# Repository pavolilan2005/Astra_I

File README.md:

# Astra_I
Diseño y desarrollo de un CubeSat experimental de bajo costo, basado en una OBC STM32F411, orientado a adquisición de datos atmosféricos, telemetría LoRa y desarrollo de tecnologías espaciales accesibles.

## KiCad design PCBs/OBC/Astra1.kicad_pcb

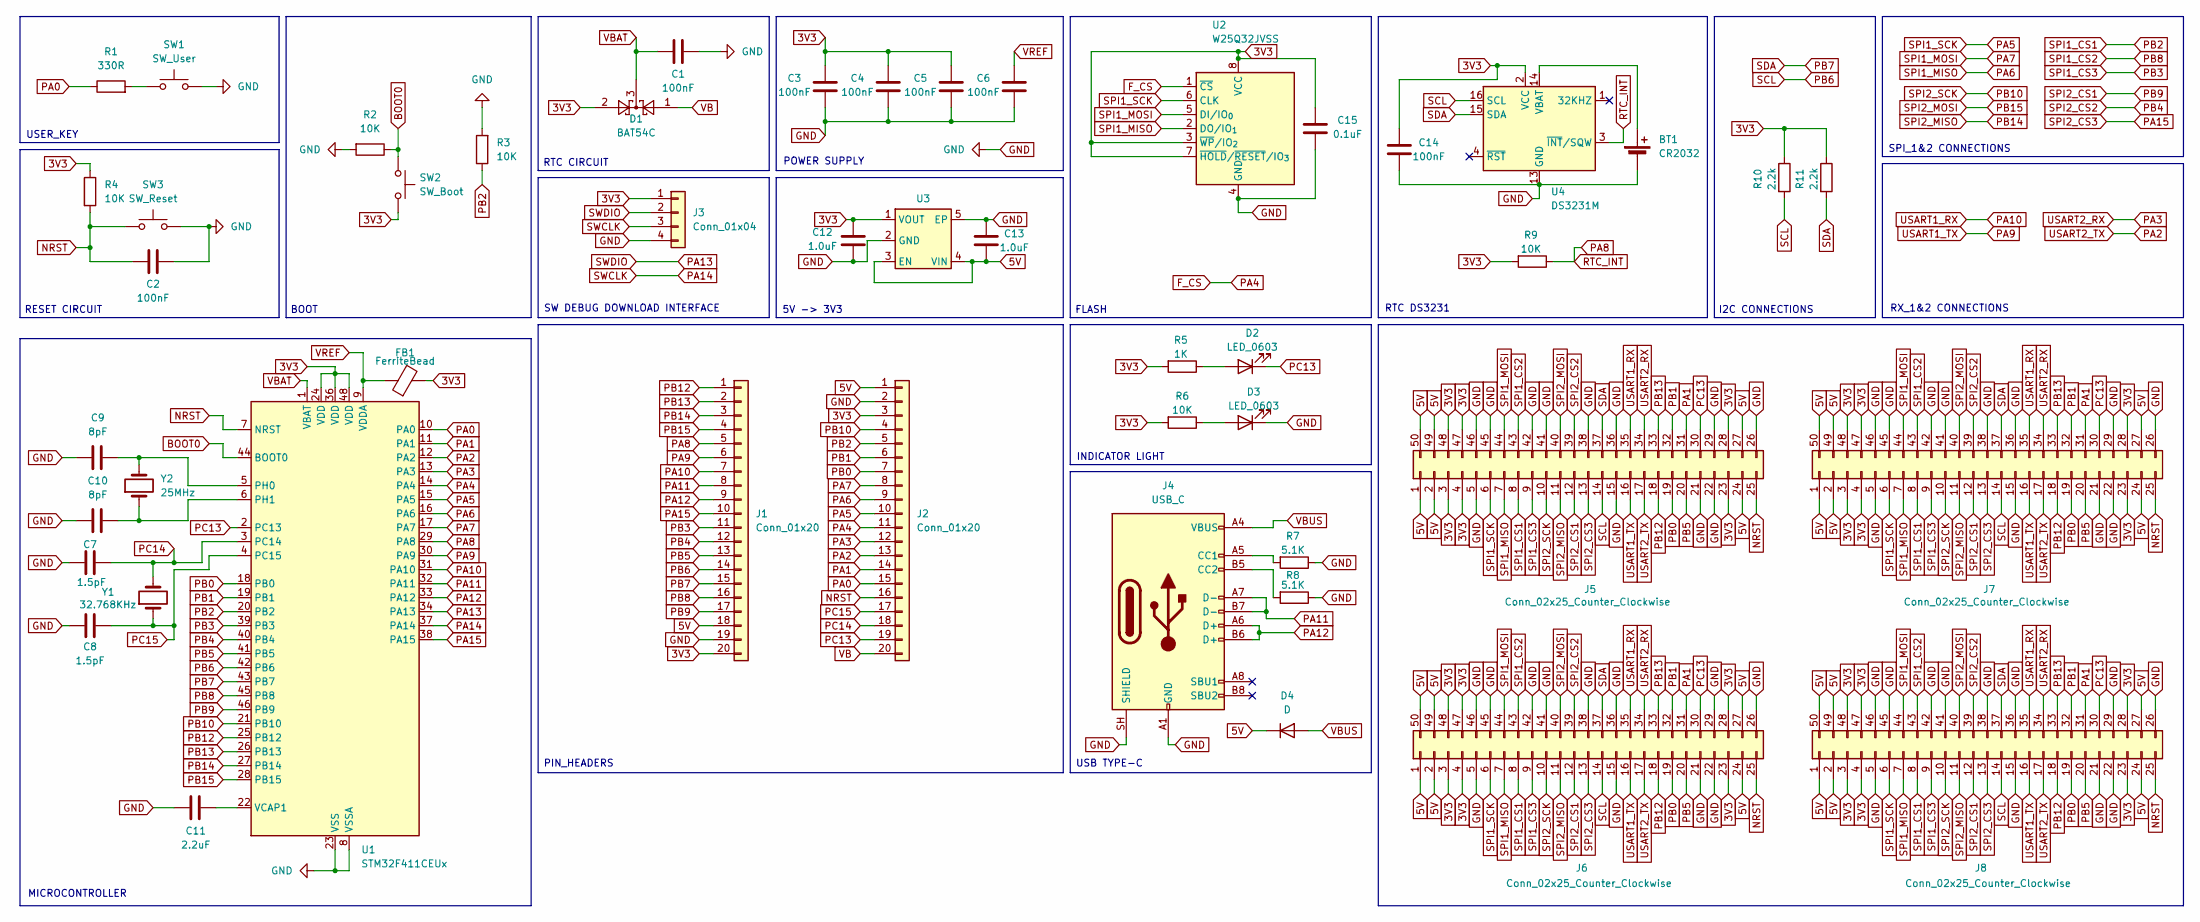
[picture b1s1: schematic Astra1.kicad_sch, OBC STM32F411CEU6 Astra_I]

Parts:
BT1: CR2032; Battery_Panasonic_CR2032-HFN_Horizontal_CircularHoles
C1, C2, C3, C4, C5, C6, C14: 100nF; C_0603_1608Metric
C7, C8: 1.5pF; C_0603_1608Metric
C9, C10: 8pF; C_0603_1608Metric
C11: 2.2uF; C_0805_2012Metric
C12, C13: 1.0uF; C_0603_1608Metric
C15: 0.1uF; C_0603_1608Metric
D1: BAT54C; SOT-23
D2, D3: LED_0603; LED_0603_1608Metric
D4: D; D_SOD-323
FB1: FerriteBead; L_0603_1608Metric
J1, J2: Conn_01x20; PinHeader_1x20_P2.54mm_Vertical
J3: Conn_01x04; PinHeader_1x04_P2.54mm_Horizontal
J4: USB_C; USB_C_Receptacle_HRO_TYPE-C-31-M-12
J5, J6, J7, J8: Conn_02x25_Counter_Clockwise; PinHeader_2x25_P2.54mm_Vertical
R1: 330R; R_0603_1608Metric
R2, R3, R4, R6, R9: 10K; R_0603_1608Metric
R5: 1K; R_0603_1608Metric
R7, R8: 5.1K; R_0603_1608Metric
R10, R11: 2.2k; R_0603_1608Metric
SW1: SW_User; SW_SPST_TL3305C
SW2: SW_Boot; SW_SPST_TL3305C
SW3: SW_Reset; SW_SPST_TL3305C
U1: STM32F411CEUx; QFN-48-1EP_7x7mm_P0.5mm_EP5.6x5.6mm
U2: W25Q32JVSS; SOIC-8_5.3x5.3mm_P1.27mm
U3: SOT-23-5
U4: DS3231M; SOIC-16W_7.5x10.3mm_P1.27mm
Y1: 32.768KHz; Crystal_SMD_2016-4Pin_2.0x1.6mm
Y2: 25MHz; Crystal_SMD_3215-2Pin_3.2x1.5mm

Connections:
3V3: C3.1, C4.1, C5.1, C12.1, C14.1, C15.2, D1.2, FB1.2, J1.20, J2.3, J3.1, J5.3, J5.4, J5.23, J5.28, J5.47, J5.48, J6.3, J6.4, J6.23, J6.28, J6.47, J6.48, J7.3, J7.4, J7.23, J7.28, J7.47, J7.48, J8.3, J8.4, J8.23, J8.28, J8.47, J8.48, R4.1, R5.2, R6.2, R9.2, R10.1, R11.1, SW2.2, U1.24 (VDD), U1.36 (VDD), U1.48 (VDD), U2.3 (~WP/IO_{2}), U2.7 (~HOLD/~RESET/IO_{3}), U2.8 (VCC), U3.1 (VOUT), U4.2 (VCC)
5V: C13.2, D4.1 (K), J1.18, J2.1, J5.1, J5.2, J5.24, J5.27, J5.49, J5.50, J6.1, J6.2, J6.24, J6.27, J6.49, J6.50, J7.1, J7.2, J7.24, J7.27, J7.49, J7.50, J8.1, J8.2, J8.24, J8.27, J8.49, J8.50, U3.3 (EN), U3.4 (VIN)
BOOT0: R2.1, SW2.1, U1.44 (BOOT0)
F_CS: J2.11, U1.14 (PA4), U2.1 (~CS)
GND: BT1.2 (-), C1.1, C2.1, C3.2, C4.2, C5.2, C6.2, C7.2, C8.2, C9.2, C10.2, C11.1, C12.2, C13.1, C14.2, C15.1, D3.1 (K), J1.19, J2.2, J3.4, J4.A1 (GND), J4.A12 (GND), J4.B1 (GND), J4.B12 (GND), J4.SH (SHIELD), J5.5, J5.15, J5.21, J5.22, J5.26, J5.29, J5.36, J5.38, J5.41, J5.42, J5.45, J5.46, J6.5, J6.15, J6.21, J6.22, J6.26, J6.29, J6.36, J6.38, J6.41, J6.42, J6.45, J6.46, J7.5, J7.15, J7.21, J7.22, J7.26, J7.29, J7.36, J7.38, J7.41, J7.42, J7.45, J7.46, J8.5, J8.15, J8.21, J8.22, J8.26, J8.29, J8.36, J8.38, J8.41, J8.42, J8.45, J8.46, R2.2, R3.2, R7.1, R8.1, SW1.2, SW3.2, U1.8 (VSSA), U1.23 (VSS), U1.35 (VSS), U1.47 (VSS), U1.49 (VSS), U2.4 (GND), U3.2 (GND), U3.5 (EP), U4.5 (GND), U4.6 (GND), U4.7 (GND), U4.8 (GND), U4.9 (GND), U4.10 (GND), U4.11 (GND), U4.12 (GND), U4.13 (GND)
NRST: C2.2, J2.16, J5.25, J6.25, J7.25, J8.25, R4.2, SW3.1, U1.7 (NRST)
unnamed: BT1.1 (+), U4.14 (VBAT)
unnamed: D2.2 (A), R5.1
unnamed: D3.2 (A), R6.1
unnamed: J4.A5 (CC1), R7.2
unnamed: J4.B5 (CC2), R8.2
unnamed: R1.2, SW1.1
unnamed: C9.1, U1.5 (PH0), Y2.2
unnamed: C10.1, U1.6 (PH1), Y2.1
unnamed: C11.2, U1.22 (VCAP1)
PA0: J2.15, R1.1, U1.10 (PA0)
PA1: J2.14, J5.31, J6.31, J7.31, J8.31, U1.11 (PA1)
PA2: J2.13, J5.17, J6.17, J7.17, J8.17, U1.12 (PA2)
PA3: J2.12, J5.34, J6.34, J7.34, J8.34, U1.13 (PA3)
PA5: J2.10, J5.6, J6.6, J7.6, J8.6, U1.15 (PA5), U2.6 (CLK)
PA6: J2.9, J5.7, J6.7, J7.7, J8.7, U1.16 (PA6), U2.2 (DO/IO_{1})
PA7: J2.8, J5.44, J6.44, J7.44, J8.44, U1.17 (PA7), U2.5 (DI/IO_{0})
PA8: J1.5, R9.1, U1.29 (PA8), U4.3 (~INT/SQW)
PA9: J1.6, J5.16, J6.16, J7.16, J8.16, U1.30 (PA9)
PA10: J1.7, J5.35, J6.35, J7.35, J8.35, U1.31 (PA10)
PA11: J1.8, J4.A7 (D-), J4.B7 (D-), U1.32 (PA11)
PA12: J1.9, J4.A6 (D+), J4.B6 (D+), U1.33 (PA12)
PA13: J3.2, U1.34 (PA13)
PA14: J3.3, U1.37 (PA14)
PA15: J1.10, J5.13, J6.13, J7.13, J8.13, U1.38 (PA15)
PB0: J2.7, J5.19, J6.19, J7.19, J8.19, U1.18 (PB0)
PB1: J2.6, J5.32, J6.32, J7.32, J8.32, U1.19 (PB1)
PB2: J2.5, J5.8, J6.8, J7.8, J8.8, R3.1, U1.20 (PB2)
PB3: J1.11, J5.9, J6.9, J7.9, J8.9, U1.39 (PB3)
PB4: J1.12, J5.39, J6.39, J7.39, J8.39, U1.40 (PB4)
PB5: J1.13, J5.20, J6.20, J7.20, J8.20, U1.41 (PB5)
PB6: J1.14, J5.14, J6.14, J7.14, J8.14, R10.2, U1.42 (PB6), U4.16 (SCL)
PB7: J1.15, J5.37, J6.37, J7.37, J8.37, R11.2, U1.43 (PB7), U4.15 (SDA)
PB8: J1.16, J5.43, J6.43, J7.43, J8.43, U1.45 (PB8)
PB9: J1.17, J5.12, J6.12, J7.12, J8.12, U1.46 (PB9)
PB10: J2.4, J5.10, J6.10, J7.10, J8.10, U1.21 (PB10)
PB12: J1.1, J5.18, J6.18, J7.18, J8.18, U1.25 (PB12)
PB13: J1.2, J5.33, J6.33, J7.33, J8.33, U1.26 (PB13)
PB14: J1.3, J5.11, J6.11, J7.11, J8.11, U1.27 (PB14)
PB15: J1.4, J5.40, J6.40, J7.40, J8.40, U1.28 (PB15)
PC13: D2.1 (K), J2.19, J5.30, J6.30, J7.30, J8.30, U1.2 (PC13)
PC14: C7.1, J2.18, U1.3 (PC14), Y1.2
PC15: C8.1, J2.17, U1.4 (PC15), Y1.1
VB: D1.1, J2.20
VBAT: C1.2, D1.3, U1.1 (VBAT)
VBUS: D4.2 (A), J4.A4 (VBUS), J4.A9 (VBUS), J4.B4 (VBUS), J4.B9 (VBUS)
VREF: C6.1, FB1.1, U1.9 (VDDA)

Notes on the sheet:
5V -> 3V3
RESET CIRCUIT
BOOT
RX_1&2 CONNECTIONS
SW DEBUG DOWNLOAD INTERFACE
PIN_HEADERS
POWER SUPPLY
MICROCONTROLLER
RTC DS3231
USER_KEY
INDICATOR LIGHT
SPI_1&2 CONNECTIONS
I2C CONNECTIONS
FLASH
USB TYPE-C
RTC CIRCUIT

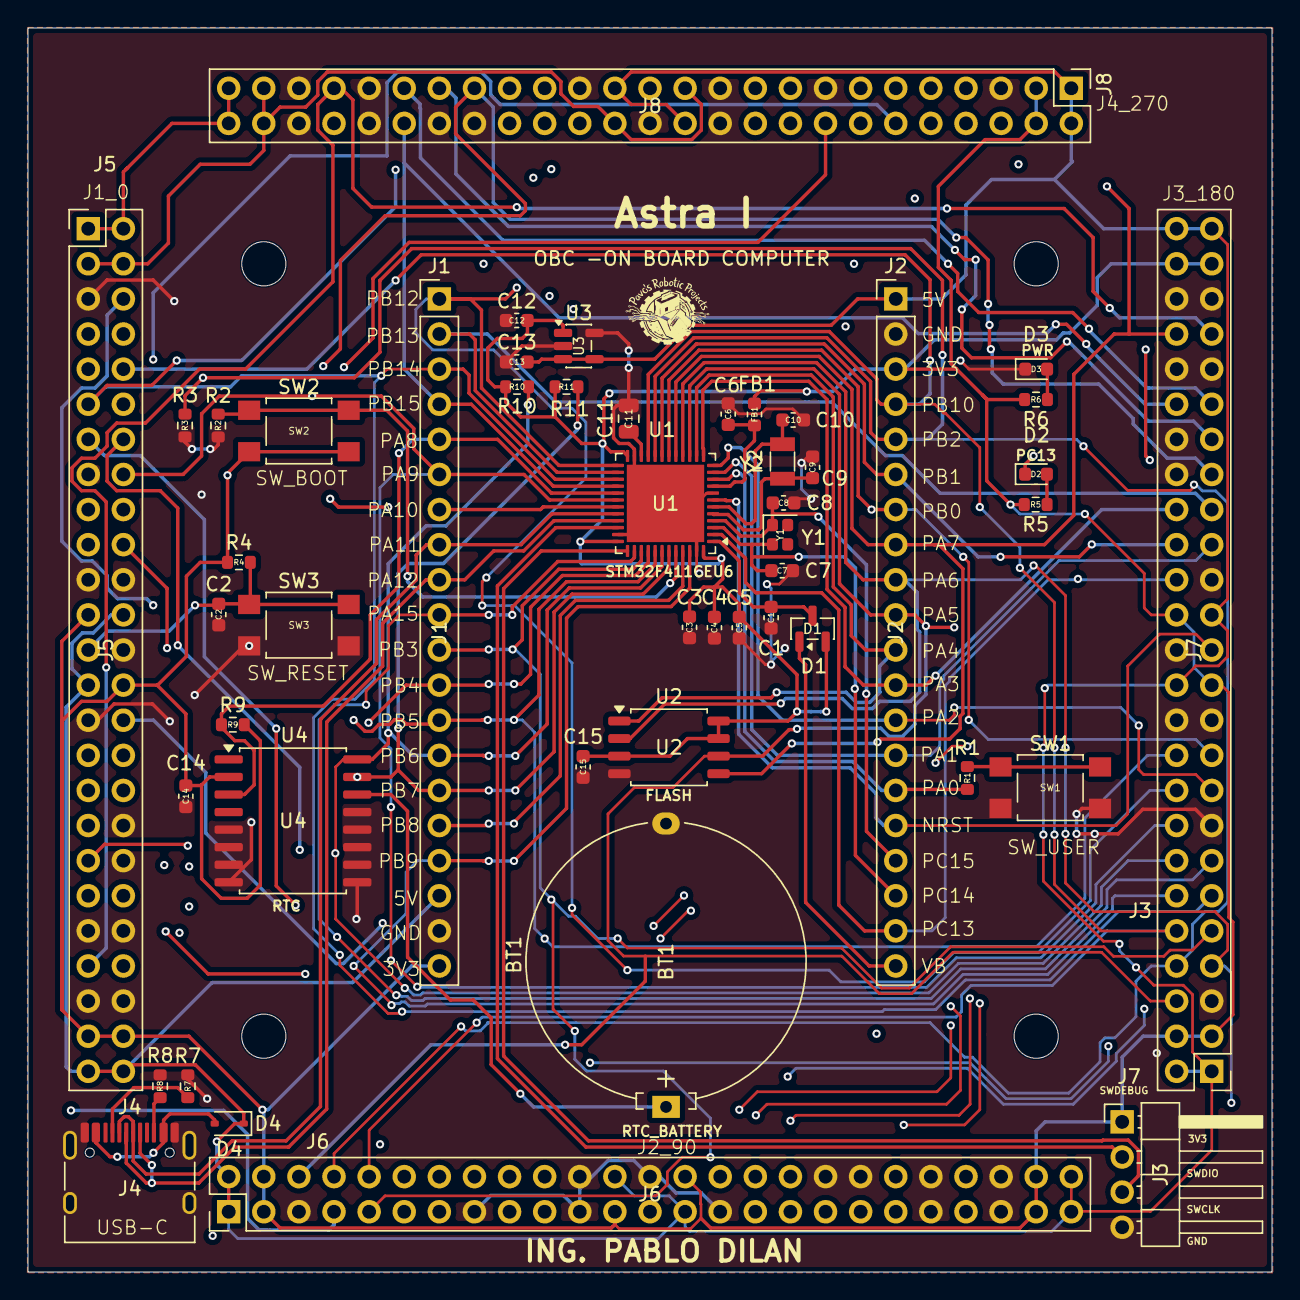
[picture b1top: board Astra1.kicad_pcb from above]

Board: 4 copper layers, 90.0 x 90.0 mm, 49 parts (0 on the bottom side), 52 nets.

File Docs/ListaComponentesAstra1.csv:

"Reference","Qty","Value","DNP","Exclude from BOM","Exclude from Board","Exclude from Simulation","Exclude from Position Files","Footprint","Datasheet"
"BT1","1","CR2032","","","","","${EXCLUDE_FROM_POS_FILES}","Battery:Battery_Panasonic_CR2032-HFN_Horizontal_CircularHoles",""
"C1,C2,C3,C4,C5,C6,C14","7","100nF","","","","","${EXCLUDE_FROM_POS_FILES}","Capacitor_SMD:C_0603_1608Metric",""
"C7,C8","2","1.5pF","","","","","${EXCLUDE_FROM_POS_FILES}","Capacitor_SMD:C_0603_1608Metric",""
"C9,C10","2","8pF","","","","","${EXCLUDE_FROM_POS_FILES}","Capacitor_SMD:C_0603_1608Metric",""
"C11","1","2.2uF","","","","","${EXCLUDE_FROM_POS_FILES}","Capacitor_SMD:C_0805_2012Metric",""
"C12,C13","2","1.0uF","","","","","${EXCLUDE_FROM_POS_FILES}","Capacitor_SMD:C_0603_1608Metric",""
"C15","1","0.1uF","","","","","${EXCLUDE_FROM_POS_FILES}","Capacitor_SMD:C_0603_1608Metric",""
"D1","1","BAT54C","","","","","${EXCLUDE_FROM_POS_FILES}","Package_TO_SOT_SMD:SOT-23","http://www.diodes.com/_files/datasheets/ds11005.pdf"
"D2,D3","2","LED_0603","","","","","${EXCLUDE_FROM_POS_FILES}","LED_SMD:LED_0603_1608Metric",""
"D4","1","D","","","","","${EXCLUDE_FROM_POS_FILES}","Diode_SMD:D_SOD-323",""
"FB1","1","FerriteBead","","","","","${EXCLUDE_FROM_POS_FILES}","Inductor_SMD:L_0603_1608Metric",""
"J1,J2","2","Conn_01x20","","","","","${EXCLUDE_FROM_POS_FILES}","Connector_PinHeader_2.54mm:PinHeader_1x20_P2.54mm_Vertical",""
"J3","1","Conn_01x04","","","","","${EXCLUDE_FROM_POS_FILES}","Connector_PinHeader_2.54mm:PinHeader_1x04_P2.54mm_Horizontal",""
"J4","1","USB_C","","","","","${EXCLUDE_FROM_POS_FILES}","Connector_USB:USB_C_Receptacle_HRO_TYPE-C-31-M-12","https://www.usb.org/sites/default/files/documents/usb_type-c.zip"
"J5,J6,J7,J8","4","Conn_02x25_Counter_Clockwise","","","","","${EXCLUDE_FROM_POS_FILES}","Connector_PinHeader_2.54mm:PinHeader_2x25_P2.54mm_Vertical",""
"R1","1","330R","","","","","${EXCLUDE_FROM_POS_FILES}","Resistor_SMD:R_0603_1608Metric",""
"R2,R3,R4,R6,R9","5","10K","","","","","${EXCLUDE_FROM_POS_FILES}","Resistor_SMD:R_0603_1608Metric",""
"R5","1","1K","","","","","${EXCLUDE_FROM_POS_FILES}","Resistor_SMD:R_0603_1608Metric",""
"R7,R8","2","5.1K","","","","","${EXCLUDE_FROM_POS_FILES}","Resistor_SMD:R_0603_1608Metric",""
"R10,R11","2","2.2k","","","","","${EXCLUDE_FROM_POS_FILES}","Resistor_SMD:R_0603_1608Metric",""
"SW1","1","SW_User","","","","","${EXCLUDE_FROM_POS_FILES}","Button_Switch_SMD:SW_SPST_TL3305C",""
"SW2","1","SW_Boot","","","","","${EXCLUDE_FROM_POS_FILES}","Button_Switch_SMD:SW_SPST_TL3305C",""
"SW3","1","SW_Reset","","","","","${EXCLUDE_FROM_POS_FILES}","Button_Switch_SMD:SW_SPST_TL3305C",""
"U1","1","STM32F411CEUx","","","","","${EXCLUDE_FROM_POS_FILES}","Package_DFN_QFN:QFN-48-1EP_7x7mm_P0.5mm_EP5.6x5.6mm","https://www.st.com/resource/en/datasheet/stm32f411ce.pdf"
"U2","1","W25Q32JVSS","","","","","${EXCLUDE_FROM_POS_FILES}","Package_SO:SOIC-8_5.3x5.3mm_P1.27mm","http://www.winbond.com/resource-files/w25q32jv%20revg%200327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"
"U3","1","","","","","","${EXCLUDE_FROM_POS_FILES}","Package_TO_SOT_SMD:SOT-23-5",""
"U4","1","DS3231M","","","","","${EXCLUDE_FROM_POS_FILES}","Package_SO:SOIC-16W_7.5x10.3mm_P1.27mm","http://datasheets.maximintegrated.com/en/ds/DS3231.pdf"
"Y1","1","32.768KHz","","","","","${EXCLUDE_FROM_POS_FILES}","Crystal:Crystal_SMD_2016-4Pin_2.0x1.6mm",""
"Y2","1","25MHz","","","","","${EXCLUDE_FROM_POS_FILES}","Crystal:Crystal_SMD_3215-2Pin_3.2x1.5mm",""
